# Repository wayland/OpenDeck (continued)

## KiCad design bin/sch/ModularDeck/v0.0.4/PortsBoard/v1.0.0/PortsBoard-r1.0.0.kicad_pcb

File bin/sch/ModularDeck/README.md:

# ModularBoard

The ModularBoard concept is that every setup will start off with a singular 
Base Board attached to any number of Breakout Boards.  These Breakout Boards can 
be of different varieties, but share a common pin header daisychain.

The intention is that, if the major version (the 1 in v1.0.0) is the same, then 
the pin headers will be the same.

The boards are as follows:
-	**Base Board:** Contains all the necessary components for an OpenDeck board; 
	basically the OpenDeck 3, but with all the parts in the Breakout boards 
	removed.
-	**Classic Breakout Board:** This plus a BaseBoard is basically an OpenDeck 3 
	with a few minor changes
-	**Standard Breakout Board:** Like the Classic Breakout Board, except:
	-	Only one Analog MUX, but the board can chain better
	-	Only 1 set of buttons
-	**3x3 Breakout Board:** Designed for lots of buttons with LEDs; supporting 
	boards are:
	-	3x3 keypad (x4)
	-	2x2 keypad (x3)

## Base Board

**Description:** Contains all the necessary components for an OpenDeck board; 
basically the OpenDeck 3, but with all the parts in the Breakout boards removed.

**Schematic:** [Base Board](https://github.com/wayland/OpenDeck/blob/master/bin/sch/ModularDeck/BaseBoard/v1.0.0/ModularDeck-r1.0.0.pdf)

### Planning
-	**Status:** Schematic complete, no PCB
-	**Intention:** Tim will do PCB if no-one else does

### Features
-	**Power:** Micro USB (Arduino Nano 33 BLE) or USB C (Black Pill)
-	**MCU:** nRF52840 (Arduino Nano 33 BLE) or STM32F411CE (Black Pill)
-	**DIN MIDI:** Yes
-	**DMX:** Yes
-	**LED indicators:** Yes
-	**ModularDeck Output Header:** 1

## Classic Breakout Board

**Description:** This plus a BaseBoard is basically an OpenDeck 3, except that the 
74HCT125 is replaced with a TXB0104PW (so that we can daisy-chain out the LEDs).
Doesn't daisy-chain the MUXs very well (see Standard Breakout Board for that).

**Schematic:** [Classic Breakout Board](https://github.com/wayland/OpenDeck/blob/master/bin/sch/ModularDeck/ClassicBreakoutBoard/v1.0.0/ClassicBreakoutBoard.pdf)

### Planning
-	**Status:** Schematic complete, no PCB
-	**Intention:** None

### Features
-	**ModularDeck Input Header:** 1
-	**ModularDeck Output Header:** 1 (Straight Through)
-	**Digital inputs:** 128
-	**Digital outputs:** 64
-	**Analog inputs:** 64

## Standard Breakout Board

**Description:** Like the Classic Breakout Board, except:
-	Only one Analog MUX, but the board can chain better
-	Only 1 set of buttons

**Schematic:** [Standard Breakout Board](https://github.com/wayland/OpenDeck/blob/master/bin/sch/ModularDeck/StandardBreakoutBoard/v1.0.0/StandardBreakoutBoard.pdf)

### Planning
-	**Status:** Schematic complete, no PCB
-	**Intention:** None

### Features
-	**ModularDeck Input Header:** 1
-	**ModularDeck Output Header:** 1 (Analog Shift 1)
-	**Digital inputs:** 64
-	**Digital outputs:** 64
-	**Analog inputs:** 16

## 3x3 Breakout Board

**Description:** Has headers for 3x3 and 2x2 LED keypads (ie. each key has its 
own LED).  The keypads have their own circuit boards (which do the diodes).

**Intended use:** For places that do speaking events with one or more speakers 
giving a presentation on a stage.
-	**The space:** A stage with say 7 different areas
-	**The control surface:** Has 7 different areas representing the stage areas
-	**Each area:**
	-	*Stage:* Has up to 9 devices (lights, microphones, cameras, HDMI 
		computers) associated with it
	-	*Control Surface:* Has 9 LED keys (3x3) representing the different 
		devices for the area.  Some stage areas might warrant fewer devices, and 
		only need a 2x2 keypad.  There will also be extra buttons, LEDs, and 
		some pots for whatever is needed.

If more stage areas are needed, simply chain more boards together (should work 
up to at least 2, hopefully 4).

**Schematics:**
-	[3x3 Breakout Board](https://github.com/wayland/OpenDeck/blob/master/bin/sch/ModularDeck/3x3BreakoutBoard/v1.0.0/3x3BreakoutBoard.pdf)
-	[3x3 Keypad Board](https://github.com/wayland/OpenDeck/blob/master/bin/sch/ModularDeck/3x3BreakoutBoard/v1.0.0/3x3Keypad/3x3Keypad.pdf)

### Planning
-	**Status:** Schematic complete, no PCB
-	**Intention:** Tim will do PCB if no-one else does

### Features
-	**ModularDeck Input Header:** 1
-	**ModularDeck Output Header:** 1 (Analog Shift 1)
-	**3x3 keypad headers:** 4 (total of 36 LED keys)
-	**2x2 keypad headers:** 3 (total of 12 LED keys)
-	**Digital inputs:** 16 (excluding keypads)
-	**Digital outputs:** 16 (excluding keypads)
-	**Analog inputs:** 16

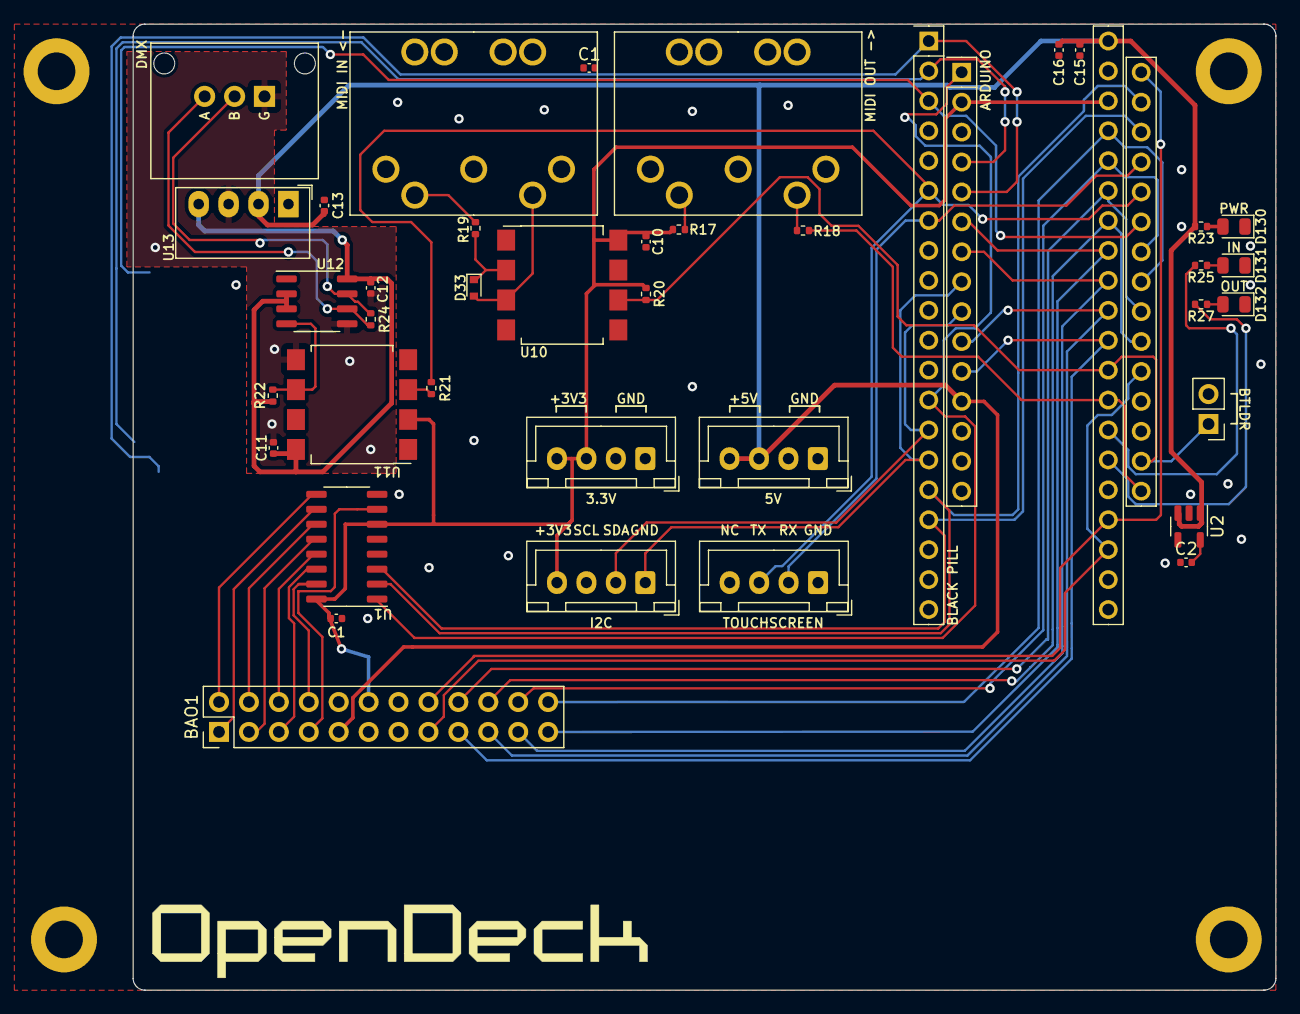
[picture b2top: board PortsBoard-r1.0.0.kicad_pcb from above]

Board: 2 copper layers, 97.0 x 82.0 mm, 44 parts (0 on the bottom side), 50 nets.

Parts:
BAO1: Conn_02x12_Odd_Even; PinHeader_2x12_P2.54mm_Vertical
C1, C1#2, C10, C11, C12, C16: 100n; C_0402_1005Metric
C2: 1u; C_0402_1005Metric
C13, C15: 10u; C_0402_1005Metric
D33: 1N4148WT; D_SOD-523
D130: Red; LED_0805_2012Metric
D131: Green; LED_0805_2012Metric
D132: Blue; LED_0805_2012Metric
H1, H2, H3, H4: MountingHole_Pad; MountingHole_3.2mm_M3_DIN965_Pad
J1, J2: DIN-5; DIN5
J3, J6, J7, J8: Conn_01x04; JST_XH_B4B-XH-A_1x04_P2.50mm_Vertical
J4: XLR3; TRAPC3MX
J5: Conn_01x02; PinHeader_1x02_P2.54mm_Vertical
R17: 33; R_0402_1005Metric
R18: 10; R_0402_1005Metric
R19: 220; R_0402_1005Metric
R20, R22: 4.7k; R_0402_1005Metric
R21: 470; R_0402_1005Metric
R23, R27: 1k; R_0402_1005Metric
R24: 133; R_0402_1005Metric
R25: 680; R_0402_1005Metric
U1: 74HC138; SO-16_3.9x9.9mm_P1.27mm
U2: SPX3819M5; SOT-23-5
U10, U11: 6N137; SSO-8_6.7x9.8mm_P2.54mm_Clearance8mm
U12: MAX485; SO-8_3.9x4.9mm_P1.27mm
U13: RFM-0505
U15: STM32F4_Black_Pill; STM32F4BlackPill
U16: Arduino_Nano_33; Arduino Nano 33 BLE

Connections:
+3.3VADC: C2.2, U2.5 (OUT)
+3V3: BAO1.12, C1.2, C1#2.2, C10.2, J6.4, J7.3, J7.4, R17.2, R20.1, U1.6 (E3), U1.16 (VCC), U10.8 (VCC), U11.2 (A), U15.38 (+3v3), U16.2 (+3V3)
+5V: BAO1.9, C13.2, C15.2, C16.2, J8.3, J8.4, R23.1, U2.1 (IN), U2.3 (EN), U13.2 (+Vin), U15.40 (+5V), U16.12 (+5V)
+5VD: C11.2, C12.2, R22.1, U11.8 (VCC), U12.2 (~RE), U12.3 (DE), U12.8 (VCC), U13.4 (+Vout)
/BC_0: BAO1.7, U1.7 (~Y7)
/BC_1: BAO1.8, U1.15 (~Y0)
/BC_2: BAO1.5, U1.14 (~Y1)
/BC_3: BAO1.6, U1.13 (~Y2)
/BC_4: BAO1.3, U1.12 (~Y3)
/BC_5: BAO1.4, U1.11 (~Y4)
/BC_6: BAO1.1, U1.10 (~Y5)
/BC_7: BAO1.2, U1.9 (~Y6)
/DEC_DI_A0: U1.1 (A0), U15.13 (B5), U16.1 (D13)
/DEC_DI_A1: U1.2 (A1), U15.16 (B8), U16.29 (D11)
/DEC_DI_A2: U1.3 (A2), U15.17 (B9), U16.28 (D10)
/DMX_TSCREEN_TX: J3.3, R21.1, U15.6 (A9), U16.26 (D8)
/MAX7219_DIN: BAO1.16, U15.24 (C15), U16.30 (D12)
/MAX7219_LOAD: BAO1.15, U15.23 (C14), U16.20 (D2)
/MIDI_RX: J5.1, R20.2, U10.6 (VO), U15.29 (A3), U16.17 (RX)
/MIDI_TX: R18.2, U15.28 (A2), U16.16 (TX)
/MUX_COMMON_1: BAO1.17, U15.30 (A4), U16.11 (A7)
/MUX_COMMON_2: BAO1.19, U15.31 (A5), U16.10 (A6)
/MUX_COMMON_3: BAO1.21, U15.32 (A6), U16.7 (A3)
/MUX_COMMON_4: BAO1.23, U15.33 (A7), U16.6 (A2)
/MUX_S0: BAO1.18, U15.35 (B1), U16.22 (D4)
/MUX_S1: BAO1.20, U15.34 (B0), U16.21 (D3)
/MUX_S2: BAO1.22, U15.36 (B2), U16.24 (D6)
/MUX_S3: BAO1.24, U15.37 (B10), U16.23 (D5)
/SCL: J6.2, U15.14 (B6), U16.9 (A5)
/SDA: J6.1, U15.15 (B7), U16.8 (A4)
/SPI_CLK: BAO1.11, U15.2 (B13), U16.4 (A0)
/SR_IN_DATA: BAO1.13, U15.3 (B14), U16.25 (D7)
/SR_IN_LATCH: BAO1.14, U15.1 (B12), U16.5 (A1)
/TRAFFIC_IN: R25.1, U15.27 (A1)
/TRAFFIC_OUT: R27.1, U15.26 (A0/Key)
/TSCREEN_RX: J3.2, U15.7 (A10), U16.27 (D9)
GND: BAO1.10, C1.1, C1#2.1, C2.1, C10.1, C13.1, C15.1, C16.1, D130.1 (K), D131.1 (K), D132.1 (K), H1.1, H2.1, H3.1, H4.1, J1.2, J3.1, J5.2, J6.3, J7.1, J7.2, J8.1, J8.2, U1.4 (~E1), U1.5 (~E2), U1.8 (GND), U2.2 (GND), U10.5 (GND), U13.1 (-Vin), U15.19 (GND), U15.39 (GND), U16.14 (GND), U16.19 (GND)
GND1: C11.1, C12.1, J4.1, U11.5 (GND), U12.5 (GND), U13.3 (-Vout)
unnamed: D33.1 (K), R19.2, U10.2 (A)
unnamed: D33.2 (A), J2.5, U10.3 (C)
unnamed: D130.2 (A), R23.2
unnamed: D131.2 (A), R25.2
unnamed: D132.2 (A), R27.2
unnamed: J1.4, R17.1
unnamed: J1.5, R18.1
unnamed: J2.4, R19.1
unnamed: J4.2, R24.1, U12.7 (B)
unnamed: J4.3, R24.2, U12.6 (A)
unnamed: R21.2, U11.3 (C)
unnamed: R22.2, U11.6 (VO), U12.4 (DI)

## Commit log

2022-09-08 Initial checkin of ModularDeck. Schematics only at this stage.
2022-09-17 Finalised schematics for ModularDeck v1.0.0 (but probably really 0.0.1
2022-09-17 Updated README to go with previous commit
2022-09-17 - Fixed markdown problems for previous version - Added bullet list of boards
2022-09-17 - Fixed markdown from previous rounds - Added a better writeup of the 3x3 board
2022-09-17 Tried to make use for 3x3 clearer.
2022-09-17 Added PDFs
2022-09-17 Added links for schematics
2022-09-17 Markdown fixes
2022-09-22 First round of bugfixes arising from https://github.com/shanteacontrols/OpenDeck/discussions/173
2022-09-22 - Linked out to logical button diagram from README - Identified keypads on button diagram - Made button diagram colours mildly less terrifying
2023-01-04 config: temporarily remove opendeck2 board from hw test rig
2023-01-10 buttons: remove special handling of preset change button on press
2023-01-31 Final changes to 0.0.4 before redoing for 0.1.1
2023-01-31 Moving for better versioning
2023-01-31 Rename ModularDeck to MOOD (MOdular OpenDeck)
2023-01-31 Base motherboard on OpenDeck
2023-02-04 Finished version 0.1.1 of motherboard
2023-02-15 - Made a bunch of changes - Added KeyboardCard
2023-02-15 ...and updated .gitignore
2023-02-15 Removed some .bak files
2023-02-17 Redid power switching
2023-02-23 - Hopefully finished schematics - Started desining PCB for motherboard
2023-03-25 Finalised schematic and PCB for MOOD Motherboard
